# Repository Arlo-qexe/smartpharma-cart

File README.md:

<div align="center">

# 🛒💊 SmartPharma Cart

**Carrito mecatrónico que lee el lote y la fecha de vencimiento de cada caja de medicamento y la clasifica físicamente según el criterio FEFO.**

*Proyecto de Diseño Mecatrónico · Ingeniería en Mecatrónica · Universidad Militar Nueva Granada (UMNG) · Semestre IX · 2026*

<sub>Del CAD en SolidWorks (izquierda) al prototipo construido (centro) y al plato con su manipulador esférico paralelo impreso en 3D (derecha).</sub>

[📘 Manual técnico](docs/manual/Manual_Tecnico_SmartPharma_Cart_v1.pdf) ·
[🎞️ Presentación final](docs/presentacion/SmartPharma_Cart_Presentacion_final.pdf) ·
[📰 Flyer](docs/presentacion/SmartPharma_Cart_Flyer_triptico.pdf) ·
[🎥 Videos](#-videos-del-proyecto) ·
[🧪 Informes FEM](docs/fem/)

</div>

---

## 📑 Contenido

1. [El problema](#-el-problema)
2. [Qué hace SmartPharma Cart](#-qué-hace-smartpharma-cart)
3. [Arquitectura del sistema](#-arquitectura-del-sistema)
4. [El prototipo](#-el-prototipo)
5. [Panel del regente (interfaz)](#-panel-del-regente-interfaz)
6. [Simulador del manipulador esférico paralelo (SPM)](#-simulador-del-manipulador-esférico-paralelo-spm)
7. [Visión artificial e IA](#-visión-artificial-e-ia)
8. [Electrónica y PCB](#-electrónica-y-pcb)
9. [Análisis de elementos finitos (FEM)](#-análisis-de-elementos-finitos-fem)
10. [Pruebas del prototipo](#-pruebas-del-prototipo)
11. [Videos del proyecto](#-videos-del-proyecto)
12. [Documentación](#-documentación)
13. [Estructura del repositorio](#-estructura-del-repositorio)
14. [Equipo](#-equipo)
15. [Para desarrollar en este repositorio](#-para-desarrollar-en-este-repositorio)

---

## 🎯 El problema

Revisar fechas de vencimiento en una droguería consume horas y falla con los empaques brillantes o troquelados. La encuesta del proyecto (34 personas entre regentes, auxiliares, droguerías y usuarios) mostró que:

| | |
|---|---|
| **67,6 %** | dedica más de 15 horas al mes a revisar vencimientos |
| **85,3 %** | tiene dificultad para leer fechas en cajas brillantes o troqueladas |
| **73,5 %** | prefiere comprar el equipo en lugar de rentarlo |

**Objetivo del proyecto:** desarrollar un carrito mecatrónico automatizado que clasifique cajas de medicamentos de 10 a 30 g, con lote y fecha impresos en tinta, en tres rangos de vencimiento según FEFO, mediante visión artificial, y que derive a **revisión manual** las cajas sin lote o fecha legibles.

> **FEFO** (*First Expired, First Out*): sale primero lo que vence primero. Por eso el carrito separa las cajas según cuánto les falta para vencer.

---

## ⚙️ Qué hace SmartPharma Cart

El regente deja las cajas en el dispensador y arranca el recorrido desde el panel. Cada caja recorre seis pasos:

1. **Carga:** el regente deja la caja en el dispensador y da la orden de inicio.
2. **Presentación:** el dispensador empuja la caja al plato de clasificación.
3. **Captura:** el plato (manipulador esférico paralelo) la gira y la cámara fotografía cada cara.
4. **Lectura:** el módulo de visión detecta la zona de lote/fecha, aplica OCR y vota entre las caras.
5. **Decisión:** el sistema calcula el destino FEFO.
6. **Clasificación:** el plato se inclina y la caja cae al cajón correspondiente; el evento queda registrado.

| Destino | Cajón | Criterio |
|---|---|---|
| `TIPO_A` | 🔴 Rojo | Vencimiento más próximo: 90 días o menos |
| `TIPO_B` | 🟡 Amarillo | Vencimiento intermedio: de 91 a 180 días |
| `TIPO_C` | ⚪ Blanco | Vencimiento lejano: más de 180 días |
| `DESCARTE` | — | Lote o fecha sin leer, o decisión del regente: el plato se detiene y la persona procesa la caja a mano |

> Los rangos de días son configurables: se cambian en el módulo de reconocimiento, no en el firmware.

---

## 🧠 Arquitectura del sistema

Cuatro niveles, con un principio central: **flujo de control estrictamente secuencial**. Ningún nodo avanza al siguiente objeto sin una confirmación explícita del actual, lo que elimina condiciones de carrera sin locks ni IDs de correlación.

```
ESP32-S3  <--UART-->  Orange Pi Zero 2W  <--TCP/mDNS-->  PC  <--Panel web-->  Regente de farmacia
(control físico        (gateway: cámara,                 (servidor, IA,
 en tiempo real)        giros y red)                      inventario y registro)
```

| Subsistema | Hardware principal | Función |
|---|---|---|
| **Chasis y tracción** | Tubular de aluminio 20×20, paredes de MDF, 2 ruedas traseras de 6 in con motores 210:1 y 2 rodachinas | Soportar todo y desplazar el carrito |
| **Gabinetes** | 3 cajones con rieles de extensión y toboganes impresos | Recibir las cajas clasificadas |
| **Dispensador** | Motor 12 V con encoder, piñón de 14 dientes y cremallera de 263 mm, ESP32-S3 SuperMini + TB6612FNG | Entregar una caja a la vez al plato |
| **Plato SPM** | Manipulador esférico paralelo, 3 motorreductores JGA25-370, engranes 17/37 en PETG, 2 drivers DRV8833 | Girar la caja y volcarla hacia el cajón |
| **Visión** | Cámara Arducam USB HDR 1080p, soporte impreso, detector YOLOv8n + OCR | Fotografiar las caras y leer lote y vencimiento |
| **Control y comunicación** | ESP32-S3 N16R8 en PCB propia, Orange Pi Zero 2W, PC | Ejecutar el ciclo y registrar cada evento |
| **Energía** | Batería de plomo-ácido sellada 12 V / 12 Ah, 3 reguladores XL4015 (10 V, 5 V, 3,3 V) | Alimentar electrónica y motores |

**Comunicaciones:** UART a 115 200 baudios con suma de verificación XOR (ESP32-S3 ↔ Orange Pi), TCP 5000/5001 con descubrimiento mDNS (Orange Pi ↔ PC) y panel HTTP en el puerto 8080. El contrato de mensajes vive en [`shared/`](shared/) y está documentado en [`docs/arquitectura_comunicacion.md`](docs/arquitectura_comunicacion.md).

---

## 🏗️ El prototipo

<table>
<tr>
<td width="50%"></td>
<td width="50%"></td>
</tr>
<tr>
<td align="center"><sub>SmartPharma Cart — presentación final</sub></td>
<td align="center"><sub>Prototipo durante las pruebas de la base de tracción</sub></td>
</tr>
</table>

| Parámetro | Valor |
|---|---|
| Dimensiones del chasis | 500 mm de ancho × 600 mm de fondo × 844 mm de alto |
| Masa del chasis | ≈ 18 kg |
| Plato de clasificación | Manipulador esférico paralelo de 3 motores; disco de acrílico Ø 250 mm × 4 mm |
| Carga sobre el plato | 2,8 kg soportados (la meta era 2 kg); cajas de prueba de 10 a 30 g |
| Cámara | Arducam USB HDR, 1080p a 30 fps; operada a 3264 × 2448 con enfoque manual fijo |
| Motores del plato | 3 × JGA25-370, 60 rpm a 12 V (alimentados a 10 V), reducción 103:1 |
| Motores de tracción | 2 × CQRobot Ocean 12 V, 6 W, 52 rpm, reducción 210:1 con encoder |
| Velocidad del carro | 0,16 m/s máx. del chasis, aceleración 0,25 m/s² |
| Costo de materiales | $ 2.025.834 COP (BOM efectivo) |

Todo el detalle —despiece, lista de materiales, explosionado, planos y mantenimiento— está en el [**Manual técnico**](docs/manual/Manual_Tecnico_SmartPharma_Cart_v1.pdf) (72 páginas).

---

## 🖥️ Panel del regente (interfaz)

El regente opera el carrito desde un **panel web** servido por la PC. Mirar el panel y el registro es libre; **operar** (iniciar o detener el recorrido, resolver alertas, editar el inventario) exige un turno abierto, y cada acción queda a nombre de la persona que la hizo.

<table>
<tr>
<td width="50%"></td>
<td width="50%"></td>
</tr>
<tr>
<td align="center"><b>Inicio</b> — fotos de cada cara, lectura de la IA, estado FEFO y botones <i>Iniciar recorrido</i>, <i>Detener</i> y <i>Llevar a punto</i></td>
<td align="center"><b>Prueba con el plato y la cámara reales</b> — la caja se fotografía sobre el plato SPM</td>
</tr>
<tr>
<td width="50%"></td>
<td width="50%"></td>
</tr>
<tr>
<td align="center"><b>Inventario</b> — una fila por caja, con filtros, edición y exportación a CSV</td>
<td align="center"><b>Vista agrupada</b> por medicamento y lote</td>
</tr>
<tr>
<td width="50%"></td>
<td width="50%"></td>
</tr>
<tr>
<td align="center"><b>Registro</b> — solo lectura y encadenado por hashes para detectar cualquier alteración</td>
<td align="center"><b>Telemetría</b> — estado de la ESP32-S3 y de la Orange Pi en vivo</td>
</tr>
<tr>
<td width="50%"></td>
<td width="50%"></td>
</tr>
<tr>
<td align="center"><b>Alertas</b> — el regente decide el destino de las cajas que el sistema no pudo leer</td>
<td align="center"><b>Configuración</b> — parámetros del contrato (solo lectura)</td>
</tr>
</table>

<details>
<summary>Más capturas: inicio y edición de una caja</summary>

<table>
<tr>
<td width="50%"></td>
<td width="50%"></td>
</tr>
<tr>
<td align="center">Inicio, antes de abrir turno</td>
<td align="center">Edición manual de medicamento, gramaje, lote, vencimiento y notas (queda en el registro con el antes y el después)</td>
</tr>
</table>

</details>

Guía de uso completa: [`docs/GUIA_REGENTE.md`](docs/GUIA_REGENTE.md). Código del panel: [`pc/`](pc/).

---

## 🦾 Simulador del manipulador esférico paralelo (SPM)

Antes de mover el hardware, el plato se diseña y se prueba en un **simulador propio** ([`esp32-firmware/simulador_spm/`](esp32-firmware/simulador_spm/)). Permite calcular la orientación del plato (cinemática directa e inversa), ver el mecanismo del CAD en 3D con su **mapa de colisiones**, planificar trayectorias, simular el seguimiento con motor y encoder simulados y conectarse por serial a la ESP32-S3 para mover los motores reales y ver su telemetría reflejada en el modelo 3D.

<table>
<tr>
<td width="50%"></td>
<td width="50%"></td>
</tr>
<tr>
<td align="center"><b>Vista 3D del CAD</b> con render por GPU</td>
<td align="center"><b>Espacio de trabajo</b> y zonas de colisión</td>
</tr>
<tr>
<td width="50%"></td>
<td width="50%"></td>
</tr>
<tr>
<td align="center"><b>Trayectorias</b> (SLERP, interpolación articular o jacobiana, perfil quíntico o trapezoidal)</td>
<td align="center"><b>Motores y control</b> con los modelos identificados sobre el motor real</td>
</tr>
</table>

<p align="center"><br><sub><b>Serial</b>: conexión con la ESP32-S3 real y telemetría reflejada en el modelo 3D</sub></p>

Incluye también el firmware de la ESP32-S3 con control en cascada sobre DRV8833, las ganancias identificadas (`identificacion_drv8833_pwm09/`), las trayectorias SmartPharma (cámara, clasificación y descarte) y pruebas automatizadas. Ver [`DESCRIPCION_SIMULADOR.md`](esp32-firmware/simulador_spm/docs_simulador/DESCRIPCION_SIMULADOR.md) y el [registro de cambios](esp32-firmware/simulador_spm/CAMBIOS_2026-11-06_a_09.md).

---

## 👁️ Visión artificial e IA

La cámara fotografía 4 caras por caja (opcionalmente 5). Cada foto pasa por un detector **YOLOv8n** que localiza la zona de lote y fecha, un **OCR** que la lee y una **votación entre caras** que decide el resultado.

<p align="center"><br><sub>Recortes de lote y vencimiento tomados con la cámara Arducam</sub></p>

El código de la IA está en [`IA/`](IA/) y se ejecuta dentro del proceso de la PC. Cuando el lote o la fecha no se pueden leer, la caja **no se adivina**: va a revisión manual y el regente decide.

---

## 🔌 Electrónica y PCB

Diseño en **KiCad** de la PCB de control (ESP32-S3 N16R8) y la de potencia, con esquema eléctrico, archivos Gerber y modelo STEP, en cinco iteraciones (`PCBBy2` a `PCBBy4_cont`).

- 📁 [`hardware/pcb-electronica/`](hardware/pcb-electronica/)
- 📄 [Esquema eléctrico](hardware/pcb-electronica/Esquema%20electrico.pdf) · [PCB de control](hardware/pcb-electronica/PCBB%20control.pdf) · [PCB de potencia](hardware/pcb-electronica/PCBB%20potencia.pdf)

Drivers: **DRV8833** (plato), **BTS7960** (base de tracción) y **TB6612FNG** (dispensador). Sensores: giroscopio MPU-6050, corriente ACS712 y ADC ADS111x por I2C. El mapa de pines de la ESP32-S3 está en el manual técnico (capítulo V).

---

## 🧪 Análisis de elementos finitos (FEM)

Se hizo un **FEM estático lineal** del carrito completo (CalculiX + Gmsh; peso propio y medicamentos en los cajones) para revisar la estructura de MDF y aluminio, con el SPM, el dispensador y el soporte de cámara sobre la placa superior.

<table>
<tr>
<td width="50%"></td>
<td width="50%"></td>
</tr>
<tr>
<td align="center">Tensión de von Mises en el ensamblaje completo</td>
<td align="center">Placa superior: tensión y desplazamiento</td>
</tr>
<tr>
<td width="50%"></td>
<td width="50%"></td>
</tr>
<tr>
<td align="center">Ensamblaje como cuerpo único, con el SPM y el dispensador mallados</td>
<td align="center">Detalle del SPM</td>
</tr>
</table>

Los informes con los supuestos, la verificación y el cálculo a mano están en [`docs/fem/`](docs/fem/). Las figuras de este README están en [`docs/media/fem/`](docs/media/fem/).

---
## ✅ Pruebas del prototipo

| Subsistema | Qué se comprobó |
|---|---|
| **Plato SPM** | 4 caras y 3 destinos con cajas de 30 g; 10 ciclos de las 4 caras con deriva ≤ 0,2°; ciclo de 30 a 32 s |
| **Dispensador** | 3 de 3 ciclos con cajas reales sin fallas; carrera de 75 mm en ~1,65 s, error máx. 0,18 mm, repetibilidad 0,02 mm |

Las pruebas se pueden ver en los [videos](#-videos-del-proyecto) y se detallan en el capítulo XI del [manual técnico](docs/manual/Manual_Tecnico_SmartPharma_Cart_v1.pdf).

---
## 🎥 Videos del proyecto

<div align="center">

<video src="https://raw.githubusercontent.com/Arlo-qexe/smartpharma-cart/main/docs/media/videos/00_proceso_diseno_manufactura_integracion.mp4" controls width="720"></video>

**Proceso de diseño, manufactura e integración mecatrónica** ([ver el video](docs/media/videos/00_proceso_diseno_manufactura_integracion.mp4))

</div>

| | | |
|:---:|:---:|:---:|
| <br>**Dispensador** | <br>**Clasificación a Tipo A** | <br>**3 ciclos, tobogán amarillo** |
| <br>**Lectura con cámara → Tipo C** (vence 07/28) | <br>**No leyó la fecha → descarte y revisión manual** | <br>**Simulador con el plato físico** |
| <br>**Sistema de tracción** | <br>**Tracción: trayectoria recta** | |

---

## 📚 Documentación

| Documento | Contenido |
|---|---|
| [📘 Manual técnico (PDF, 72 págs.)](docs/manual/Manual_Tecnico_SmartPharma_Cart_v1.pdf) | Mecánica, despiece y BOM, sistema eléctrico, control y comunicaciones, operación, mantenimiento, diagnóstico de fallas, seguridad y pruebas |
| [🎞️ Presentación final (PDF, 27 diapositivas)](docs/presentacion/SmartPharma_Cart_Presentacion_final.pdf) | Requisitos, diseño, control, IA, comunicación y precio de venta |
| [📰 Flyer / tríptico](docs/presentacion/SmartPharma_Cart_Flyer_triptico.pdf) | Resumen comercial del proyecto |
| [🧪 Informes FEM](docs/fem/) | Análisis de elementos finitos del carrito, con supuestos y verificación |
| [📡 Arquitectura de comunicación](docs/arquitectura_comunicacion.md) | Protocolo completo ESP32-S3 ↔ Orange Pi ↔ PC ↔ regente |
| [📝 Changelog del protocolo](docs/CHANGELOG_protocolo.md) | Historial de cambios al contrato |
| [🧑‍⚕️ Guía del regente](docs/GUIA_REGENTE.md) | Uso del panel de control |
| [✅ Checklist PC ↔ Orange Pi](shared/checklist.md) | Estado compartido, solicitudes y decisiones entre los dos lados |
| [📊 Informe de avances](shared/INFORME_AVANCES_2026-11-03.md) | Avances de PC, Orange Pi, ESP32-S3 e IA al 2026-11-03 |

---

## 🗂️ Estructura del repositorio

```
smartpharma-cart/
├── docs/                      # arquitectura, guía del regente, manual, presentación y FEM
│   ├── manual/                # manual técnico (PDF)
│   ├── presentacion/          # presentación final y flyer (PDF)
│   ├── fem/                   # informes del análisis de elementos finitos
│   └── media/                 # imágenes y videos usados en este README
├── shared/                    # contrato de comunicación — fuente única de verdad
├── esp32-firmware/            # control físico en tiempo real (C++/Arduino)
│   └── simulador_spm/         # simulador del manipulador esférico paralelo + firmware del plato
├── orange-pi/                 # gateway de captura y red (Python)
├── pc/                        # servidor, panel del regente y asistente (Python)
├── IA/                        # lectura de lote y vencimiento (YOLOv8n + OCR)
├── hardware/
│   └── pcb-electronica/       # PCB de control y de potencia (KiCad)
├── tests/integration/         # pruebas de extremo a extremo
├── scripts/hooks/             # hooks de sincronización entre agentes
└── .github/workflows/         # aviso automático a Telegram cuando cambia shared/
```

---

## 👥 Equipo

**Grupo 3 — Diseño Mecatrónico, semestre IX** · Universidad Militar Nueva Granada · Ingeniería en Mecatrónica

- Laura Daniela Castaño Silva
- Carlos Andres Quintero Forero
- Carol Tatiana Jerez González

**Profesor:** Germán Leandro Vargas

---

## 🛠️ Para desarrollar en este repositorio

Este repo está organizado para que cada persona trabaje desde su propio dispositivo (Orange Pi o PC) sin perder sincronía con el otro lado, con agentes de Claude Code que se coordinan mediante el repositorio.

1. Configura el aviso de Telegram una sola vez: [`docs/TELEGRAM_SETUP.md`](docs/TELEGRAM_SETUP.md).
2. Lee [`CLAUDE.md`](CLAUDE.md) (raíz): resumen de la arquitectura, la regla de oro y cómo se sincronizan los agentes (hooks + Telegram).
3. Entra a la carpeta que te corresponde (`orange-pi/` o `pc/`) y lee su `CLAUDE.md`.
4. Corre Claude Code **desde esa subcarpeta** (`cd orange-pi && claude` o `cd pc && claude`) para que cargue el contexto general, el específico y los hooks de sincronización.

> **Regla de oro:** nunca escribas un nombre de mensaje, un timeout o un formato de datos directamente dentro de `orange-pi/`, `pc/` o `esp32-firmware/`. Todo cambio al contrato se hace primero en [`shared/`](shared/), se documenta en [`docs/CHANGELOG_protocolo.md`](docs/CHANGELOG_protocolo.md) y se avisa al equipo antes de hacer push.

Cada lado tiene su propio entorno virtual (`bash scripts/setup_venv.sh`): `orange-pi/` es ARM64 y `pc/` es x86_64 con CUDA, así que **nunca comparten un venv**.

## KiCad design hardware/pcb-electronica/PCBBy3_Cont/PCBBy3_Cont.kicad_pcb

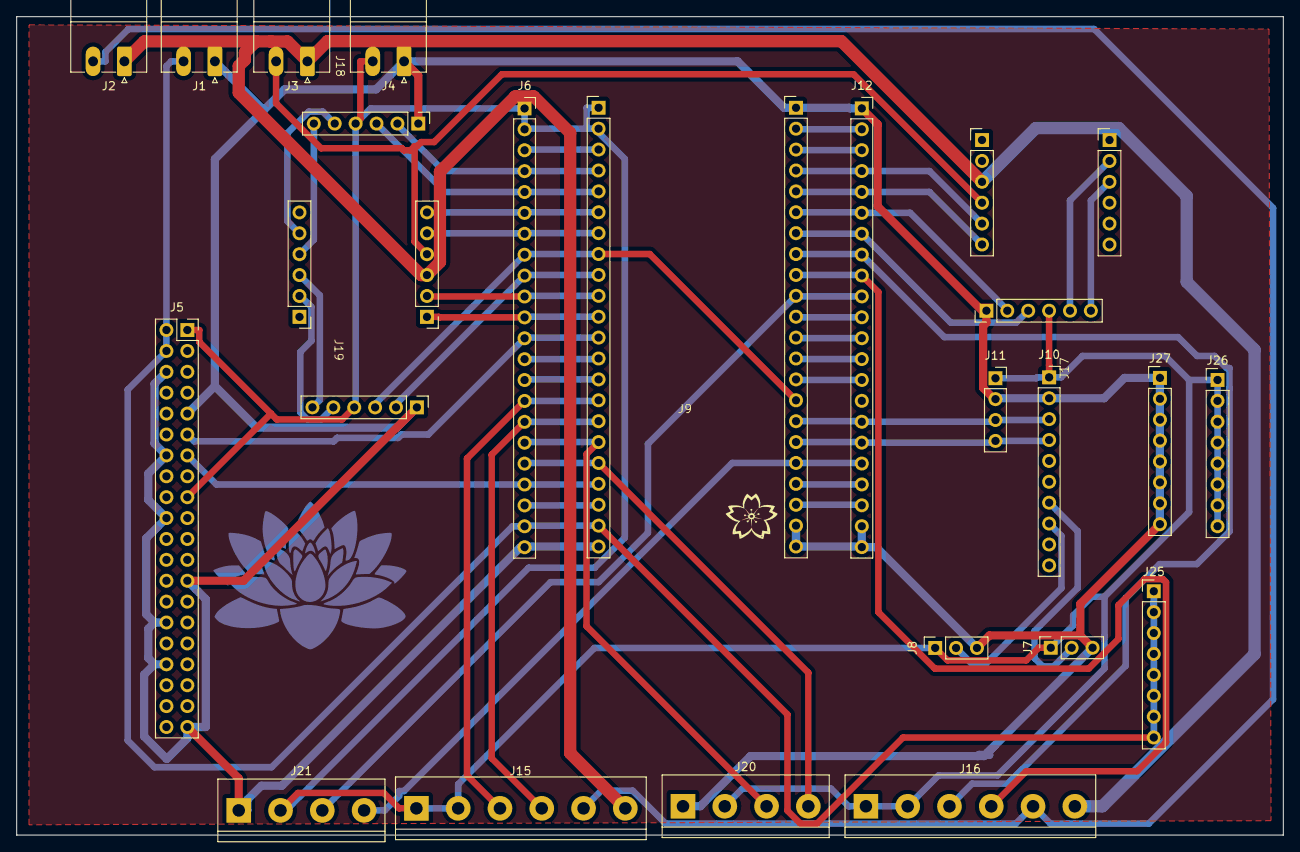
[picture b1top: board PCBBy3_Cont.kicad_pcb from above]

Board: 2 copper layers, 154.0 x 99.5 mm, 24 parts (0 on the bottom side), 50 nets.

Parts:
J1: 5v; PhoenixContact_MC_1,5_2-G-3.81_1x02_P3.81mm_Horizontal
J2: 12v; PhoenixContact_MC_1,5_2-G-3.81_1x02_P3.81mm_Horizontal
J3: 10v; PhoenixContact_MC_1,5_2-G-3.81_1x02_P3.81mm_Horizontal
J4: 3.3v; PhoenixContact_MC_1,5_2-G-3.81_1x02_P3.81mm_Horizontal
J5: Orange_Pi_Zero 2w; PinSocket_2x20_P2.54mm_Vertical
J6: Esp_L; PinSocket_1x22_P2.54mm_Vertical
J7: Amp1; PinSocket_1x03_P2.54mm_Vertical
J8: Amp2; PinSocket_1x03_P2.54mm_Vertical
J9: ESP32_S3; esp32s316
J10: ADS1115; PinSocket_1x10_P2.54mm_Vertical
J11: MPU_6050; PinSocket_1x04_P2.54mm_Vertical
J12: Esp_R; PinSocket_1x22_P2.54mm_Vertical
J13: Drv8833_2; Drv8833
J14: Drv8833_1; Drv8833
J15, J16: Conn_01x06; TerminalBlock_bornier-6_P5.08mm
J17: M1; MotorA
J18: M2; MotorA
J19: M3; MotorA
J20, J21: Conn_01x04; TerminalBlock_bornier-4_P5.08mm
J25, J26, J27: Conn_01x08; PinHeader_1x08_P2.54mm_Vertical

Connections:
+3.3V: J4.2, J5.1, J5.17, J6.1, J6.2, J7.1, J8.1, J9.3v3 (Pin_1), J10.1, J11.1, J15.1, J15.2, J16.1, J16.2, J17.VCC (Pin_4), J18.VCC (Pin_4), J19.VCC (Pin_4), J20.2, J21.2, J26.1, J26.2, J26.3, J26.4, J26.5, J26.6, J26.7, J26.8
+5V: J1.2, J5.2, J5.4, J6.21, J9.5v (Pin_21), J25.1, J25.2, J25.3, J25.4, J25.5, J25.6, J25.7, J25.8
+10V: J3.2, J13.VCC (Pin_4), J14.VCC (Pin_4)
+12V: J2.2, J15.5, J16.5
A1: J9.41 (Pin_38), J12.7, J17.A (Pin_3)
A2: J6.5, J9.5, J18.A (Pin_3)
A3: J6.8, J9.15 (Pin_8), J19.A (Pin_3)
A4: J6.17, J9.11 (Pin_17), J20.3
A5: J9.38 (Pin_35), J12.10, J21.3
ADC1: J7.2, J10.7
ADC2: J8.2, J10.8
B1: J9.42 (Pin_39), J12.6, J17.B (Pin_2)
B2: J6.4, J9.4, J18.B (Pin_2)
B3: J6.9, J9.16 (Pin_9), J19.B (Pin_2)
B4: J6.18, J9.12 (Pin_18), J20.4
B5: J9.21 (Pin_27), J12.18, J21.4
GND: J1.1, J4.1, J5.6, J5.9, J5.14, J5.20, J5.25, J5.30, J5.34, J5.39, J6.22, J7.3, J8.3, J9.GND (Pin_23), J10.2, J11.2, J12.1, J12.21, J12.22, J17.GND (Pin_1), J18.GND (Pin_1), J19.GND (Pin_1), J20.1, J21.1, J27.1, J27.2, J27.3, J27.4, J27.5, J27.6, J27.7, J27.8
GND1: J2.1, J3.1, J13.GND (Pin_3), J14.GND (Pin_3), J15.6, J16.6
M1L: J13.OUT1 (Pin_11), J17.M2 (Pin_5)
M1R: J13.OUT2 (Pin_10), J17.M1 (Pin_6)
M2L: J14.OUT4 (Pin_8), J18.M2 (Pin_5)
M2R: J14.OUT3 (Pin_9), J18.M1 (Pin_6)
M3L: J14.OUT1 (Pin_11), J19.M2 (Pin_5)
M3R: J14.OUT2 (Pin_10), J19.M1 (Pin_6)
unnamed: J6.3, J9.RST (Pin_3)
unnamed: J6.13, J9.3 (Pin_13)
unnamed: J6.14, J9.46 (Pin_14)
unnamed: J6.20, J9.14 (Pin_20)
unnamed: J9.Tx (Pin_43), J12.2
unnamed: J9.Rx (Pin_42), J12.3
unnamed: J9.1 (Pin_41), J12.4, J13.IN2 (Pin_5)
unnamed: J9.2 (Pin_40), J12.5, J13.IN1 (Pin_6)
unnamed: J9.40 (Pin_37), J12.8, J16.3
unnamed: J9.39 (Pin_36), J12.9, J16.4
unnamed: J9.37 (Pin_34), J12.11
unnamed: J9.36 (Pin_33), J12.12
unnamed: J9.35 (Pin_32), J12.13
unnamed: J9.0 (Pin_31), J12.14
unnamed: J9.20 (Pin_26), J12.19
unnamed: J9.19 (Pin_25), J12.20
unnamed: J6.11, J9.18 (Pin_11), J14.IN4 (Pin_1)
unnamed: J6.10, J9.17 (Pin_10), J14.IN3 (Pin_2)
unnamed: J6.7, J9.7, J14.IN2 (Pin_5)
unnamed: J6.6, J9.6, J14.IN1 (Pin_6)
unnamed: J6.15, J9.9 (Pin_15), J15.3
unnamed: J6.16, J9.10 (Pin_16), J15.4
Rx: J5.13, J6.19, J9.13 (Pin_19)
SCL: J9.48 (Pin_29), J10.3, J11.3, J12.16
SDA: J9.47 (Pin_28), J10.4, J11.4, J12.17
Tx: J5.11, J6.12, J9.8 (Pin_12)

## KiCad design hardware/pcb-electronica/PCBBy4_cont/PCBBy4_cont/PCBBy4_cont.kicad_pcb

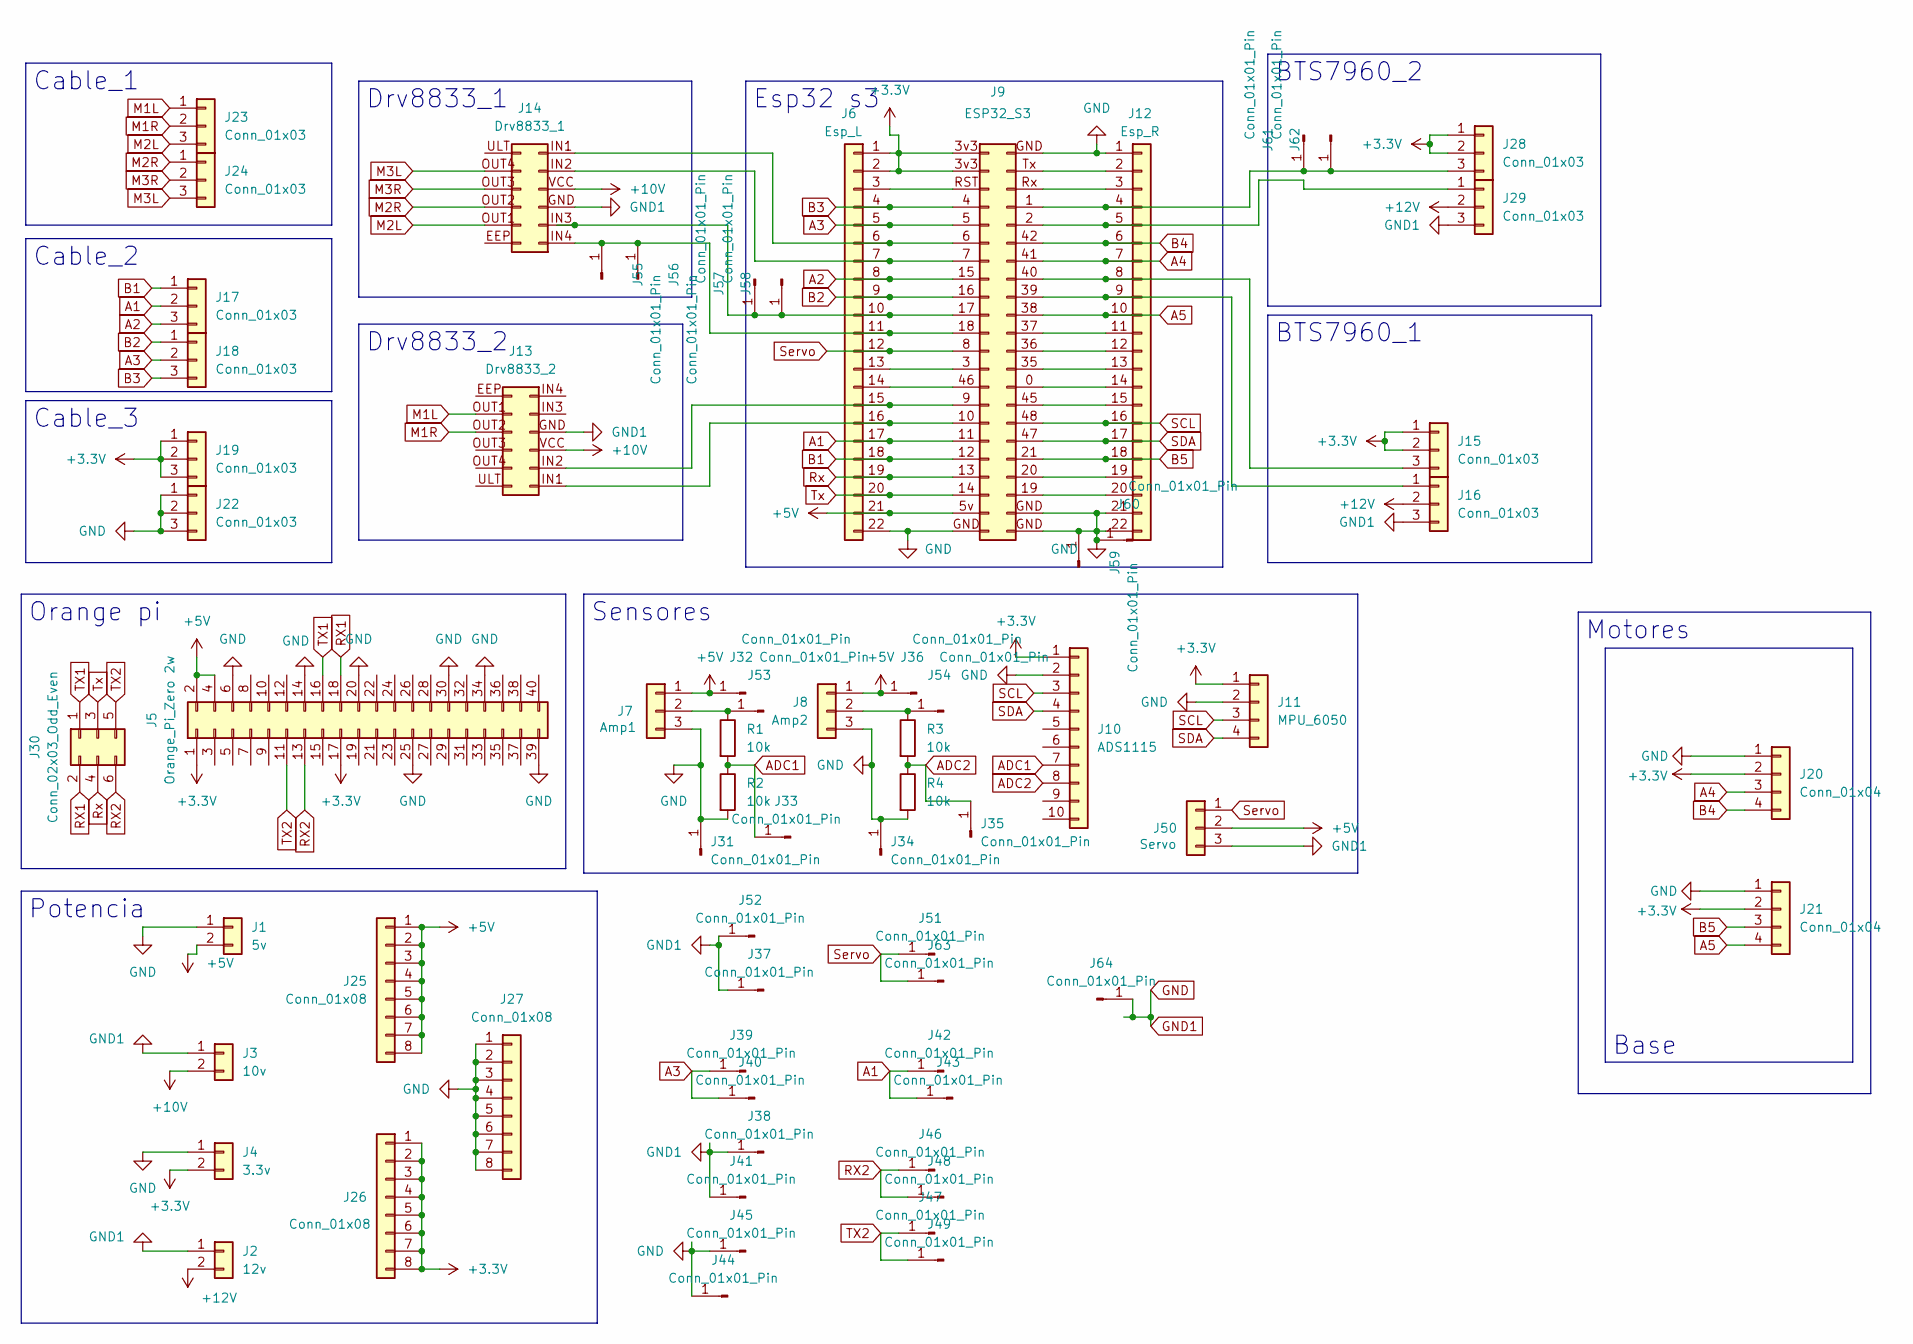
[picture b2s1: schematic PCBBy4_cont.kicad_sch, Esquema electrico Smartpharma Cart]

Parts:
J1: 5v; PhoenixContact_MC_1,5_2-G-3.81_1x02_P3.81mm_Horizontal
J2: 12v; PhoenixContact_MC_1,5_2-G-3.81_1x02_P3.81mm_Horizontal
J3: 10v; PhoenixContact_MC_1,5_2-G-3.81_1x02_P3.81mm_Horizontal
J4: 3.3v; PhoenixContact_MC_1,5_2-G-3.81_1x02_P3.81mm_Horizontal
J5: Orange_Pi_Zero 2w; PinSocket_2x20_P2.54mm_Vertical
J6: Esp_L; PinSocket_1x22_P2.54mm_Vertical
J7: Amp1; PinSocket_1x03_P2.54mm_Vertical
J8: Amp2; PinSocket_1x03_P2.54mm_Vertical
J9: ESP32_S3; esp32s316
J10: ADS1115; PinSocket_1x10_P2.54mm_Vertical
J11: MPU_6050; PinSocket_1x04_P2.54mm_Vertical
J12: Esp_R; PinSocket_1x22_P2.54mm_Vertical
J13: Drv8833_2; Drv8833
J14: Drv8833_1; Drv8833
J15, J16, J17, J18, J19, J22, J23, J24, J28, J29: Conn_01x03; PhoenixContact_MSTBVA_2,5_3-G-5,08_1x03_P5.08mm_Vertical
J20, J21: Conn_01x04; PhoenixContact_MSTBA_2,5_4-G-5,08_1x04_P5.08mm_Horizontal
J25, J26, J27: Conn_01x08; PinHeader_1x08_P2.54mm_Vertical
J30: Conn_02x03_Odd_Even; PinHeader_2x03_P2.54mm_Vertical
J31, J32, J33, J34, J35, J36, J37, J38, J39, J40, J41, J42, J43, J44, J45, J46, J47, J48, J49, J51, J52, J53, J54, J55, J56, J57, J58, J59, J60, J61, J62, J63, J64: Conn_01x01_Pin; PinHeader_1x01_P2.54mm_Vertical
J50: Servo; PinSocket_1x03_P2.54mm_Vertical
R1, R2, R3, R4: 10k; R_1206_3216Metric_Pad1.30x1.75mm_HandSolder

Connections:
+3.3V: J4.2, J5.1, J5.17, J6.1, J6.2, J9.3v3 (Pin_1), J10.1, J11.1, J15.1, J15.2, J19.1, J19.2, J19.3, J20.2, J21.2, J26.1, J26.2, J26.3, J26.4, J26.5, J26.6, J26.7, J26.8, J28.1, J28.2
+5V: J1.2, J5.2, J5.4, J6.21, J7.1, J8.1, J9.5v (Pin_21), J25.1, J25.2, J25.3, J25.4, J25.5, J25.6, J25.7, J25.8, J32.1, J36.1, J50.2
+10V: J3.2, J13.VCC (Pin_4), J14.VCC (Pin_4)
+12V: J2.2, J16.2, J29.2
A1: J6.17, J9.11 (Pin_17), J17.2, J42.1, J43.1
A2: J6.8, J9.15 (Pin_8), J17.3
A3: J6.5, J9.5, J18.2, J39.1, J40.1
A4: J9.41 (Pin_38), J12.7, J20.3
A5: J9.38 (Pin_35), J12.10, J21.4
ADC1: J10.7, J33.1, R1.2, R2.1
ADC2: J10.8, J35.1, R3.2, R4.1
B1: J6.18, J9.12 (Pin_18), J17.1
B2: J6.9, J9.16 (Pin_9), J18.1
B3: J6.4, J9.4, J18.3
B4: J9.42 (Pin_39), J12.6, J20.4
B5: J9.21 (Pin_27), J12.18, J21.3
GND: J1.1, J2.1, J3.1, J4.1, J5.6, J5.14, J5.20, J5.25, J5.30, J5.34, J5.39, J6.22, J7.3, J8.3, J9.GND (Pin_24), J10.2, J11.2, J12.1, J12.21, J12.22, J13.GND (Pin_3), J14.GND (Pin_3), J16.3, J20.1, J21.1, J22.1, J22.2, J22.3, J27.1, J27.2, J27.3, J27.4, J27.5, J27.6, J27.7, J27.8, J29.3, J31.1, J34.1, J37.1, J38.1, J41.1, J44.1, J45.1, J50.3, J52.1, J59.1, J60.1, J64.1, R2.2, R4.2
M1L: J13.OUT1 (Pin_11), J23.1
M1R: J13.OUT2 (Pin_10), J23.2
M2L: J14.OUT1 (Pin_11), J23.3
M2R: J14.OUT2 (Pin_10), J24.1
M3L: J14.OUT4 (Pin_8), J24.3
M3R: J14.OUT3 (Pin_9), J24.2
unnamed: J6.3, J9.RST (Pin_3)
unnamed: J6.13, J9.3 (Pin_13)
unnamed: J6.14, J9.46 (Pin_14)
unnamed: J9.Tx (Pin_43), J12.2
unnamed: J9.Rx (Pin_42), J12.3
unnamed: J9.1 (Pin_41), J12.4, J28.3, J61.1, J62.1
unnamed: J9.2 (Pin_40), J12.5, J29.1
unnamed: J9.40 (Pin_37), J12.8, J15.3
unnamed: J9.39 (Pin_36), J12.9, J16.1
unnamed: J9.37 (Pin_34), J12.11
unnamed: J9.36 (Pin_33), J12.12
unnamed: J9.35 (Pin_32), J12.13
unnamed: J9.0 (Pin_31), J12.14
unnamed: J9.45 (Pin_30), J12.15
unnamed: J9.20 (Pin_26), J12.19
unnamed: J9.19 (Pin_25), J12.20
unnamed: J6.15, J9.9 (Pin_15), J13.IN2 (Pin_5)
unnamed: J6.16, J9.10 (Pin_16), J13.IN1 (Pin_6)
unnamed: J6.11, J9.18 (Pin_11), J14.IN4 (Pin_1), J55.1, J56.1
unnamed: J6.10, J9.17 (Pin_10), J14.IN3 (Pin_2), J57.1, J58.1
unnamed: J6.7, J9.7, J14.IN2 (Pin_5)
unnamed: J6.6, J9.6, J14.IN1 (Pin_6)
unnamed: J7.2, J53.1, R1.1
unnamed: J8.2, J54.1, R3.1
RX1: J5.18, J30.2
RX2: J5.13, J30.6, J46.1, J48.1
Rx: J6.19, J9.13 (Pin_19), J30.4
SCL: J9.48 (Pin_29), J10.3, J11.3, J12.16
SDA: J9.47 (Pin_28), J10.4, J11.4, J12.17
Servo: J6.12, J9.8 (Pin_12), J50.1, J51.1, J63.1
TX1: J5.16, J30.1
TX2: J5.11, J30.5, J47.1, J49.1
Tx: J6.20, J9.14 (Pin_20), J30.3

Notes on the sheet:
Cable_1
Orange pi
Motores
Esp32 s3
Cable_2
Base
Drv8833_1
Sensores
BTS7960_2
Potencia
Drv8833_2
BTS7960_1
Cable_3

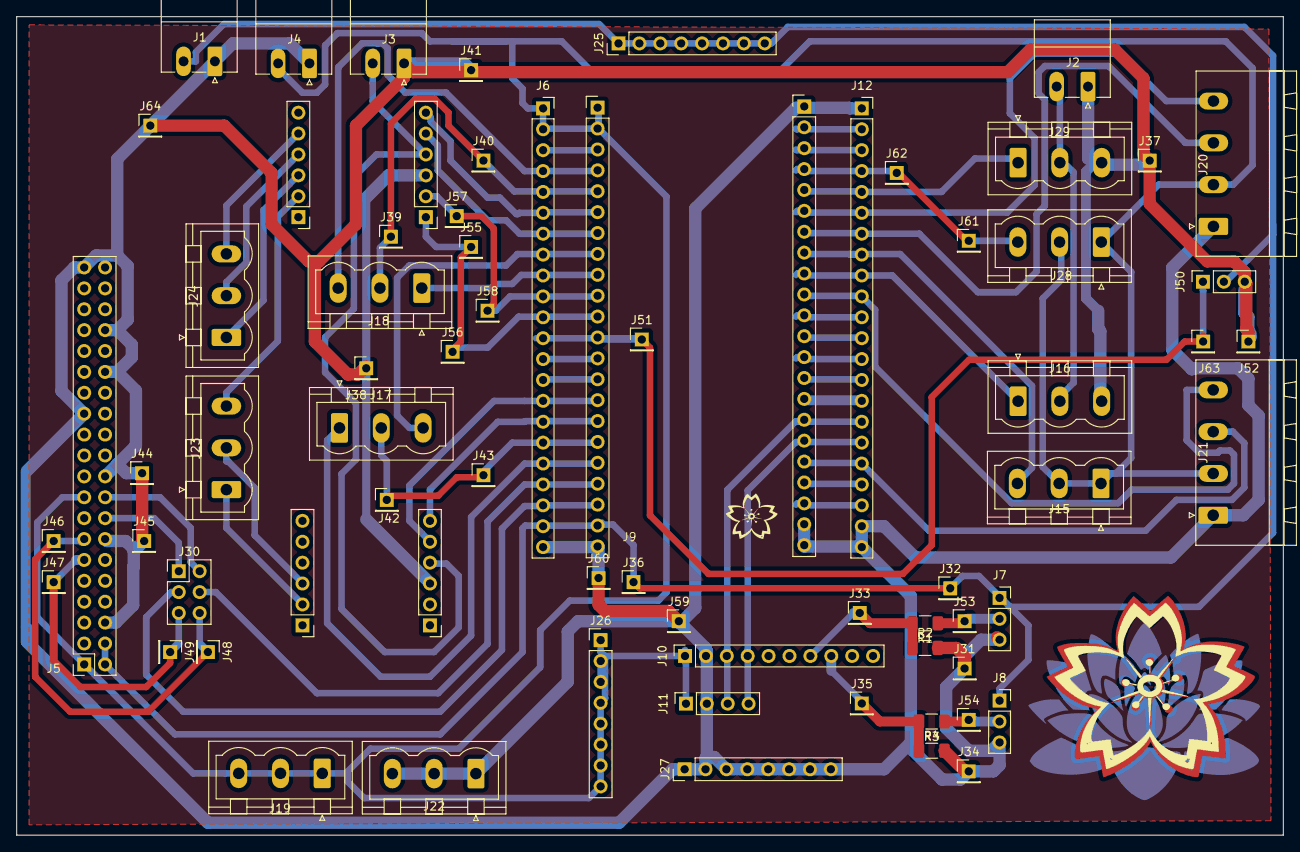
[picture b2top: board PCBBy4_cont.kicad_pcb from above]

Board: 2 copper layers, 154.0 x 99.5 mm, 68 parts (0 on the bottom side), 56 nets.

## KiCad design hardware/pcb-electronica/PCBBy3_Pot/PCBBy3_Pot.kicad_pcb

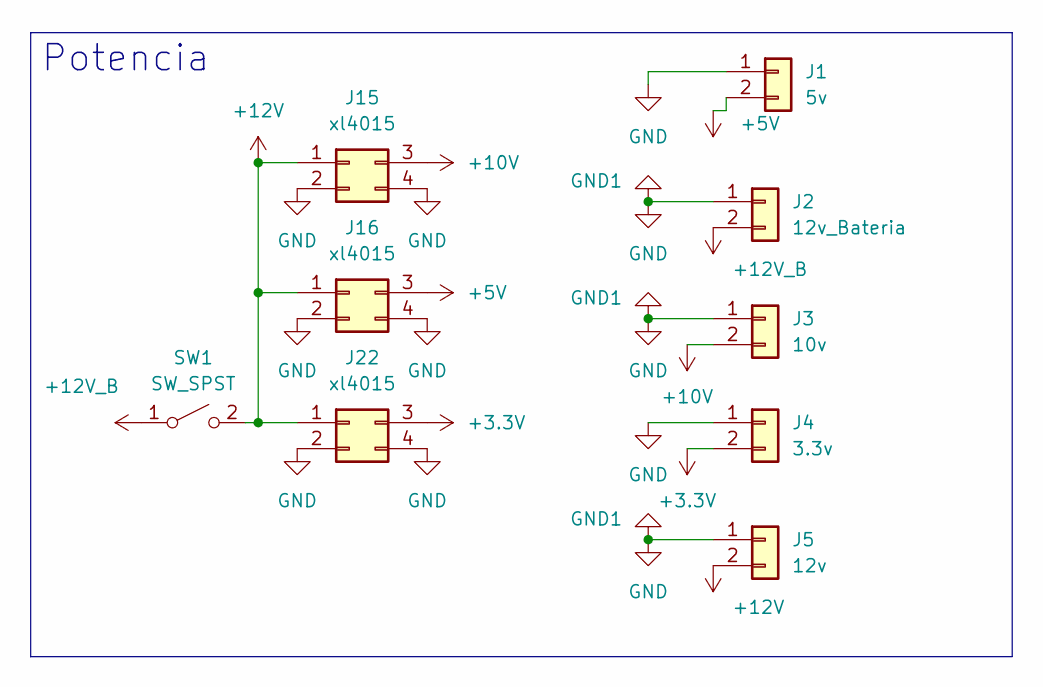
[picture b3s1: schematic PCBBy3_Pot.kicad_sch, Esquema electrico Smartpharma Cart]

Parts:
J1: 5v; PhoenixContact_MC_1,5_2-G-3.81_1x02_P3.81mm_Horizontal
J2: 12v_Bateria; PhoenixContact_MC_1,5_2-G-3.81_1x02_P3.81mm_Horizontal
J3: 10v; PhoenixContact_MC_1,5_2-G-3.81_1x02_P3.81mm_Horizontal
J4: 3.3v; PhoenixContact_MC_1,5_2-G-3.81_1x02_P3.81mm_Horizontal
J5: 12v; PhoenixContact_MC_1,5_2-G-3.81_1x02_P3.81mm_Horizontal
J15, J16, J22: xl4015; XL4005_DC-DC
SW1: SW_SPST; SW_SPST_Omron_B3F-40xx

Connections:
+3.3V: J4.2, J22.3 (Pin_4)
+5V: J1.2, J16.3 (Pin_4)
+10V: J3.2, J15.3 (Pin_4)
+12V: J5.2, J15.1, J16.1, J22.1, SW1.2 (B)
+12V_B: J2.2, SW1.1 (A)
GND: J1.1, J2.1, J3.1, J4.1, J5.1, J15.2, J15.4 (Pin_3), J16.2, J16.4 (Pin_3), J22.2, J22.4 (Pin_3)

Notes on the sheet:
Potencia

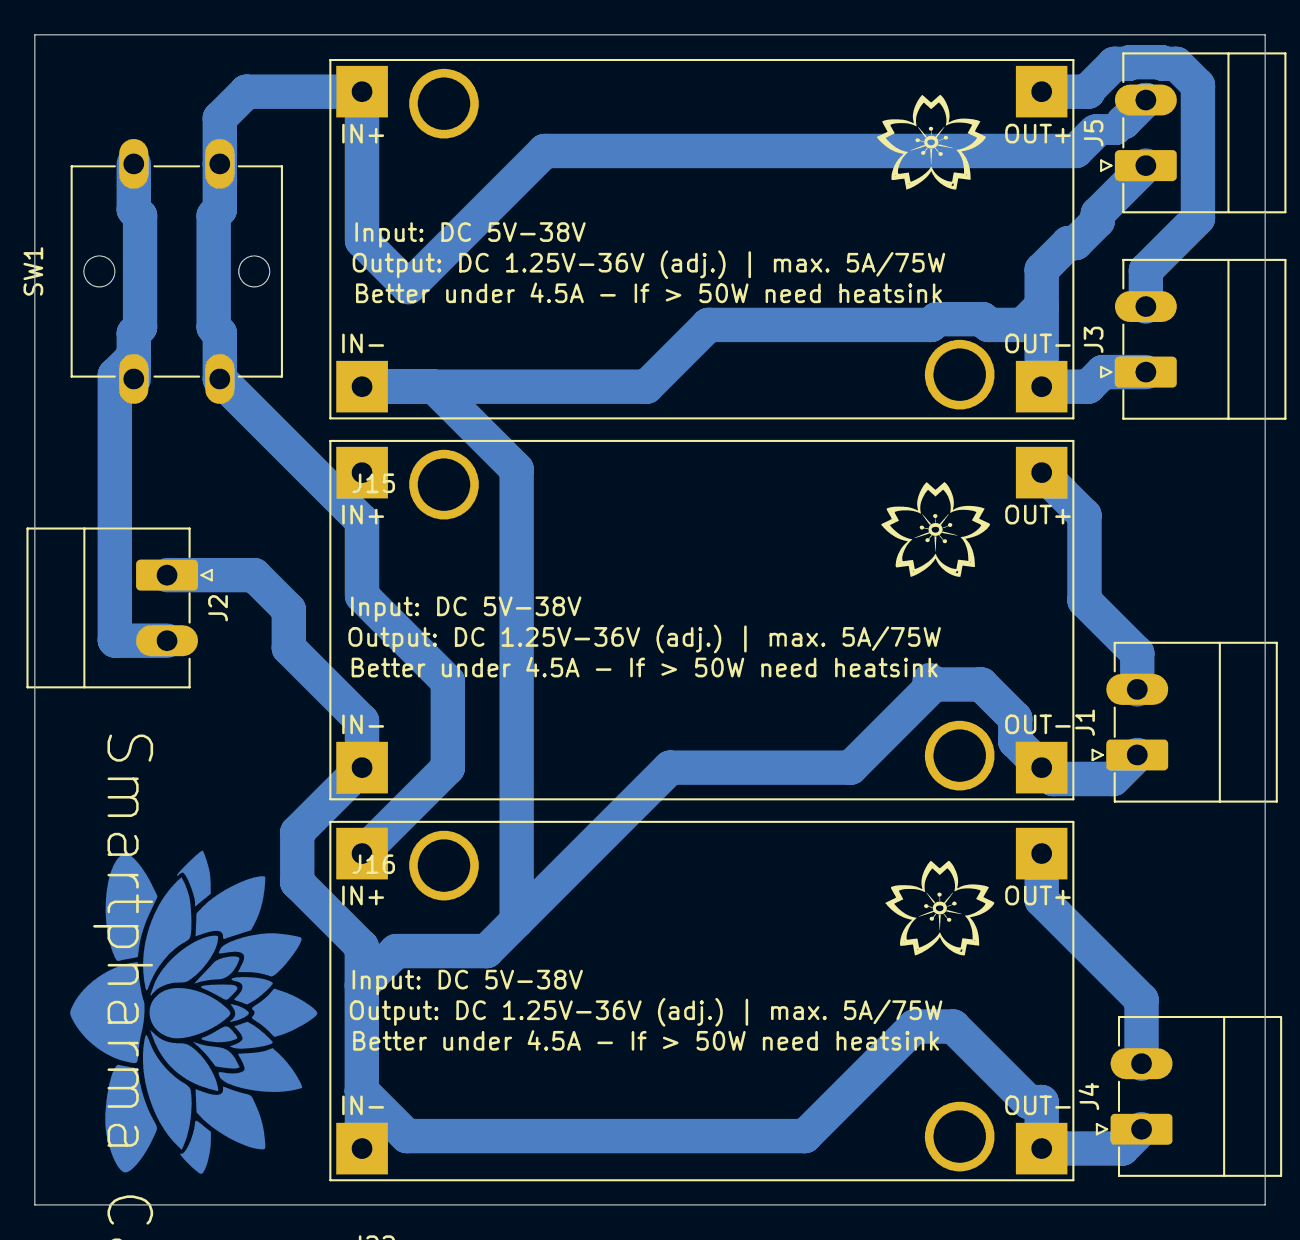
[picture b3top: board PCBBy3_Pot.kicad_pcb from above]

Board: 2 copper layers, 71.5 x 68.0 mm, 9 parts (0 on the bottom side), 6 nets.
